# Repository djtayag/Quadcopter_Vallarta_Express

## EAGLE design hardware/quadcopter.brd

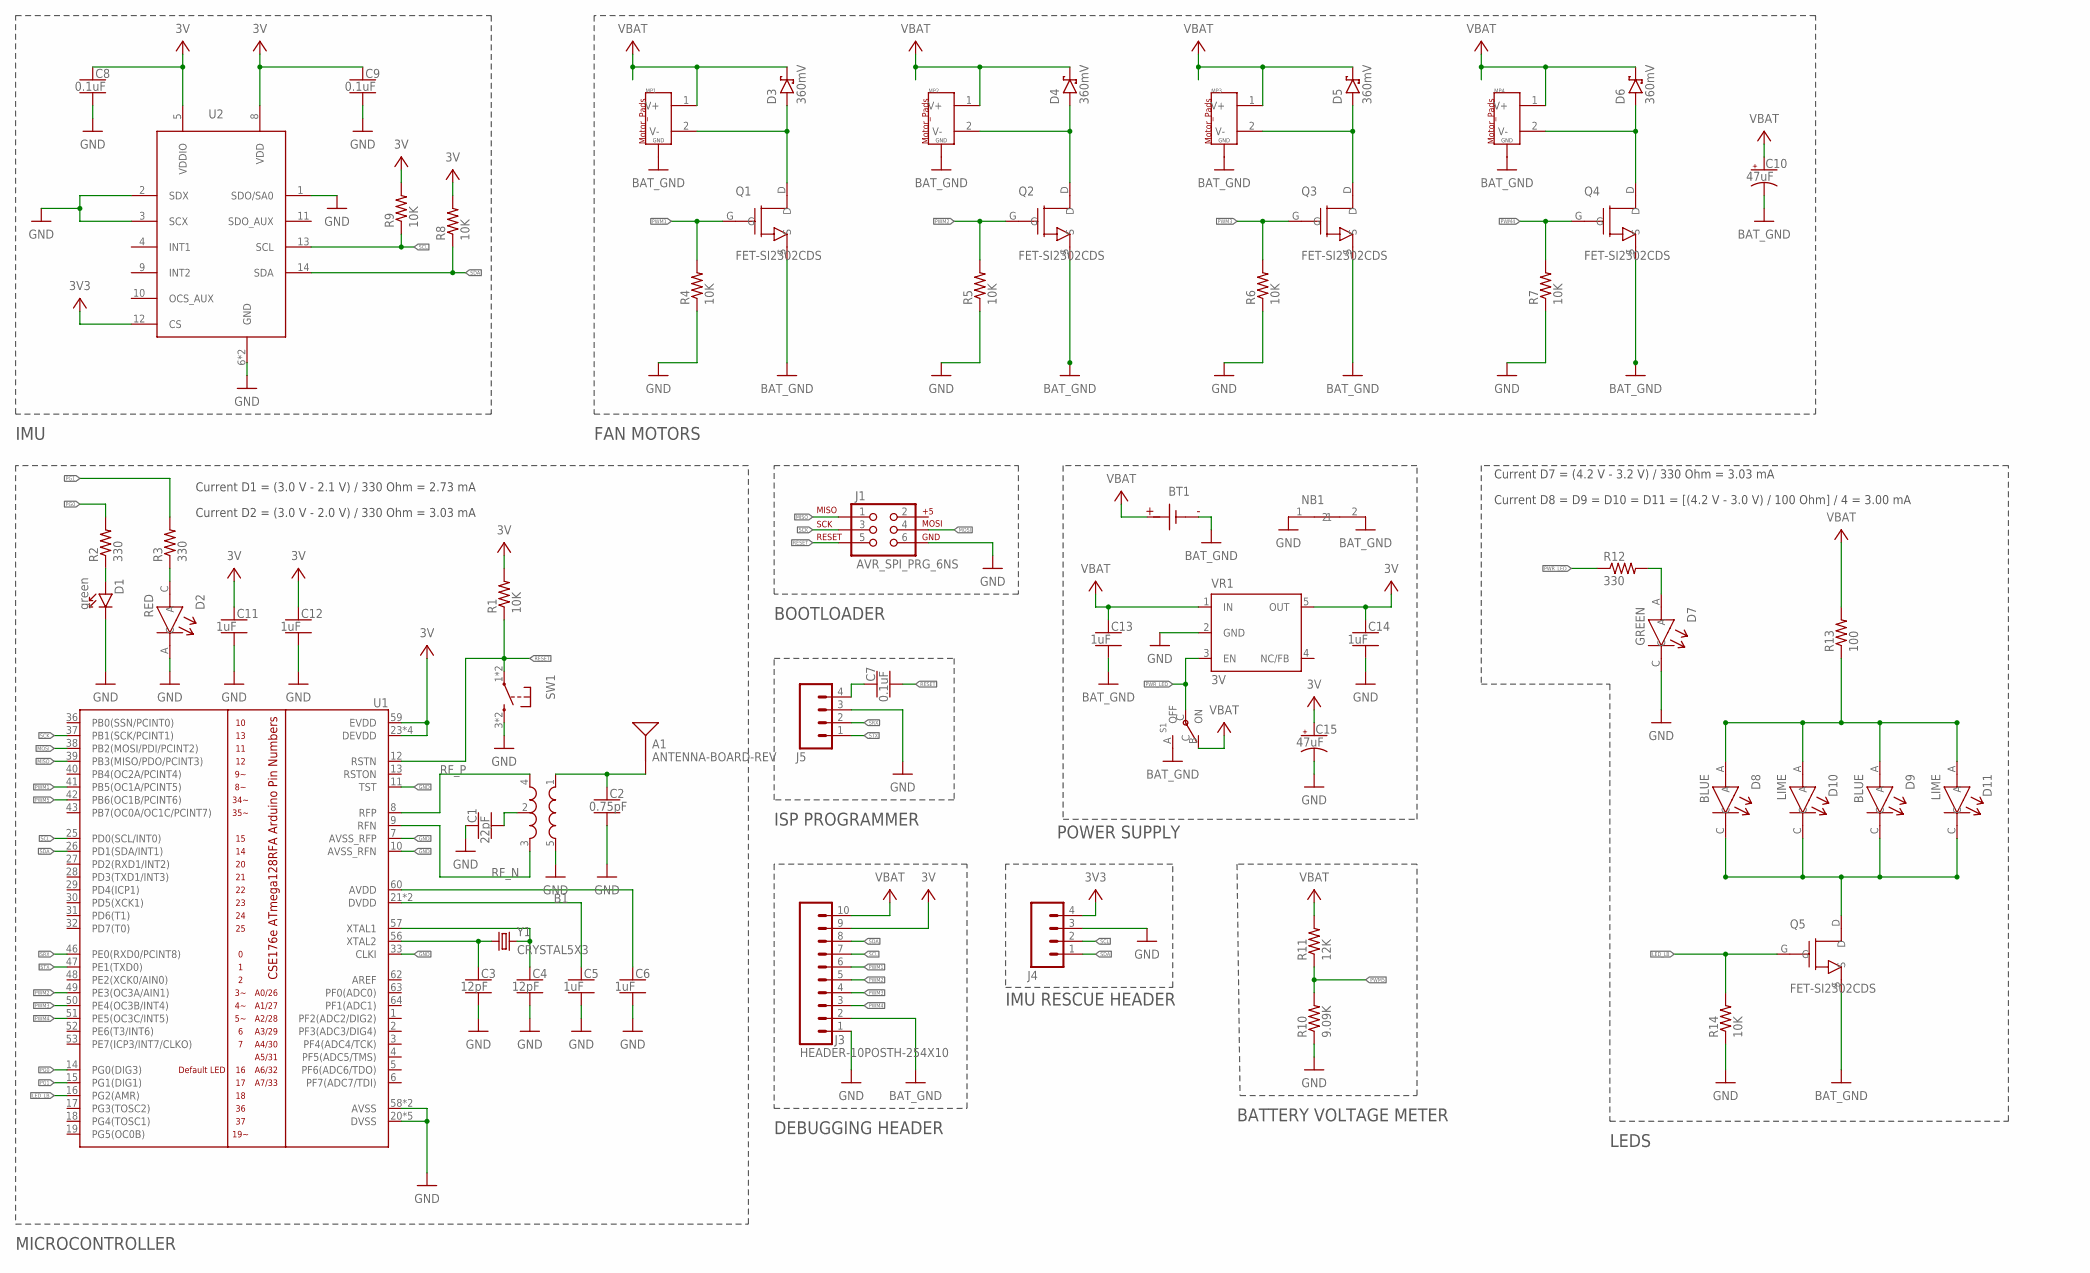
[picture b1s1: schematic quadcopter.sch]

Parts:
A1: ANTENNA-BOARD-REV; ANT_PCB_2.4GHZ_NRF8001_1.6MM_1OZ_REV
B1: BALUN0805; BALUN
BT1: BATTERY-SCREW-TERMINAL; SCREW-TERMINAL-1X2-2.54MM
C1: 22pF; CAPC2012X140_HS
C2: 0.75pF; CAPC2012X140_HS
C3, C4: 12pF; CAPC2012X140_HS
C5, C6, C11, C12, C13, C14: 1uF; CAPC2012X140_HS
C7, C8, C9: 0.1uF; CAPC2012X140_HS
C10, C15: 47uF; CAPMP3216X180
D1: green; LEDSC125X200X120-2_HS
D2: RED; 0805_LED
D3, D4, D5, D6: 360mV; SODFL3516X96
D7: GREEN; 0805_LED
D8, D9: BLUE; 1411_LED
D10, D11: LIME; 1411_LED
J1: AVR_SPI_PRG_6NS; 2X3-NS
J3: HEADER-10POSTH-254X10; HDRV10W63P254_10X1_2540X254H838_HS
J4: HEADER-4POS-0.1IN-FEMALE; HDRVR4W80P254_1X4_1066X254X850B
J5: HEADER-4POS-0.1IN-FEMALE-SMD-BOTTOM-ENTRY; HEADER-1X4-BOTTOM-ENTRY
MP1, MP2, MP3, MP4: MOTOR_PADS_GND-MOLEX-SMD; MOLEX-0532610271
NB1: NET-BRIDGE
Q1, Q2, Q3, Q4, Q5: FET-SI2302CDS; SI2302MOSFET
R1, R4, R5, R6, R7, R8, R9, R14: 10K; RESC2012X60_HS
R2, R3, R12: 330; RESC2012X60_HS
R10: 9.09K; RESC2012X60_HS
R11: 12K; RESC2012X60_HS
R13: 100; RESC2012X60_HS
S1: POWER-SWITCH-MFS201N-9-Z-SMD-EDGE; JS102011SAQN
SW1: PUSHBUTTON_SMD-VERTICAL-1; TE_FSM8JSMA_HS
U1: ATMEGA128RFA1; QFN-64
U2: IMU_LSM6DSOX-LSM6DSOXTR; LSM6DS0XTR
VR1: 3V; SOT23-DBV
Y1: CRYSTAL5X3; CRYSTAL-SMD-5X3

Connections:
3V3: C8.1, C9.1, C11.1, C12.1, C14.1, C15.1 (+), J3.9, J4.4, R1.2, R8.2, R9.2, U1.23 (DEVDD), U1.34 (DEVDD), U1.44 (DEVDD), U1.54 (DEVDD), U1.59 (EVDD), U2.5 (VDDIO), U2.8 (VDD), U2.12 (CS), VR1.5 (OUT)
BAT_GND: BT1.1 (N), C10.2 (-), C13.2, J3.2, MP1.G1 (GND), MP1.G2 (GND), MP2.G1 (GND), MP2.G2 (GND), MP3.G1 (GND), MP3.G2 (GND), MP4.G1 (GND), MP4.G2 (GND), NB1.2, Q1.S, Q2.S, Q3.S, Q4.S, Q5.S, S1.A (OFF)
GND: B1.5 (GND), C1.1, C2.2, C3.2, C4.2, C5.2, C6.2, C8.2, C9.2, C11.2, C12.2, C14.2, C15.2 (-), D1.C, D2.A (C), D7.C, J1.6, J3.1, J4.3, J5.3, NB1.1, R4.1, R5.1, R6.1, R7.1, R10.1, R14.1, SW1.3 (2), SW1.4 (2), U1.7 (AVSS_RFP), U1.10 (AVSS_RFN), U1.11 (TST), U1.20 (DVSS), U1.24 (DVSS), U1.33 (CLKI), U1.35 (DVSS), U1.45 (DVSS), U1.55 (DVSS), U1.58 (AVSS), U1.61 (AVSS), U2.1 (SDO/SA0), U2.2 (SDX), U2.3 (SCX), U2.6 (GND), U2.7 (GND), VR1.2 (GND)
LED_LB: Q5.G, R14.2, U1.16 (PG2(AMR))
MISO: J1.1, U1.39 (PB3(MISO/PDO/PCINT3))
MOSI: J1.4, U1.38 (PB2(MOSI/PDI/PCINT2))
unnamed: B1.2 (GND), C1.2
unnamed: A1.FEED, B1.1 (IN), C2.1
unnamed: D3.2 (A), MP1.2 (V-), Q1.D
unnamed: D1.A, R2.1
unnamed: C3.1, U1.56 (XTAL2), Y1.1
unnamed: C4.1, U1.57 (XTAL1), Y1.3 (2)
unnamed: C5.1, U1.21 (DVDD), U1.22 (DVDD)
unnamed: C6.1, U1.60 (AVDD)
unnamed: D4.2 (A), MP2.2 (V-), Q2.D
unnamed: D5.2 (A), MP3.2 (V-), Q3.D
unnamed: D6.2 (A), MP4.2 (V-), Q4.D
unnamed: C7.1, J5.4
unnamed: D2.C (A), R3.1
unnamed: D7.A, R12.2
unnamed: D8.A, D9.A, D10.A, D11.A, R13.1
unnamed: D8.C, D9.C, D10.C, D11.C, Q5.D
PG0: R2.2, U1.14 (PG0(DIG3))
PG1: R3.2, U1.15 (PG1(DIG1))
PWM1: J3.6, Q1.G, R4.2, U1.41 (PB5(OC1A/PCINT5))
PWM2: J3.5, Q2.G, R5.2, U1.49 (PE3(OC3A/AIN1))
PWM3: J3.4, Q3.G, R6.2, U1.50 (PE4(OC3B/INT4))
PWM4: J3.3, Q4.G, R7.2, U1.51 (PE5(OC3C/INT5))
PWM5: R10.2, R11.1, U1.42 (PB6(OC1B/PCINT6))
PWR_LED: R12.1, S1.C, VR1.3 (EN)
RESET: C7.2, J1.5, R1.1, SW1.1, SW1.2 (1), U1.12 (RSTN)
RF_N: B1.3 (OUT2), U1.9 (RFN)
RF_P: B1.4 (OUT1), U1.8 (RFP)
SCK: J1.3, U1.37 (PB1(SCK/PCINT1))
SCL: J3.7, J4.2, R9.1, U1.25 (PD0(SCL/INT0)), U2.13 (SCL)
SDA: J3.8, J4.1, R8.1, U1.26 (PD1(SDA/INT1)), U2.14 (SDA)
SRX: J5.2, U1.46 (PE0(RXD0/PCINT8))
STX: J5.1, U1.47 (PE1(TXD0))
VBAT: BT1.2, C10.1 (+), C13.1, D3.1 (C), D4.1 (C), D5.1 (C), D6.1 (C), J3.10, MP1.1 (V+), MP2.1 (V+), MP3.1 (V+), MP4.1 (V+), R11.2, R13.2, S1.B (ON), VR1.1 (IN)

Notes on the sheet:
MICROCONTROLLER
BOOTLOADER
ISP PROGRAMMER
IMU
FAN MOTORS
DEBUGGING HEADER
IMU RESCUE HEADER
POWER SUPPLY
BATTERY VOLTAGE METER
LEDS
Current D1 = (3.0 V - 2.1 V) / 330 Ohm = 2.73 mA
Current D2 = (3.0 V - 2.0 V) / 330 Ohm = 3.03 mA
Current D7 = (4.2 V - 3.2 V) / 330 Ohm = 3.03 mA
Current D8 = D9 = D10 = D11 = [(4.2 V - 3.0 V) / 100 Ohm] / 4 = 3.00 mA

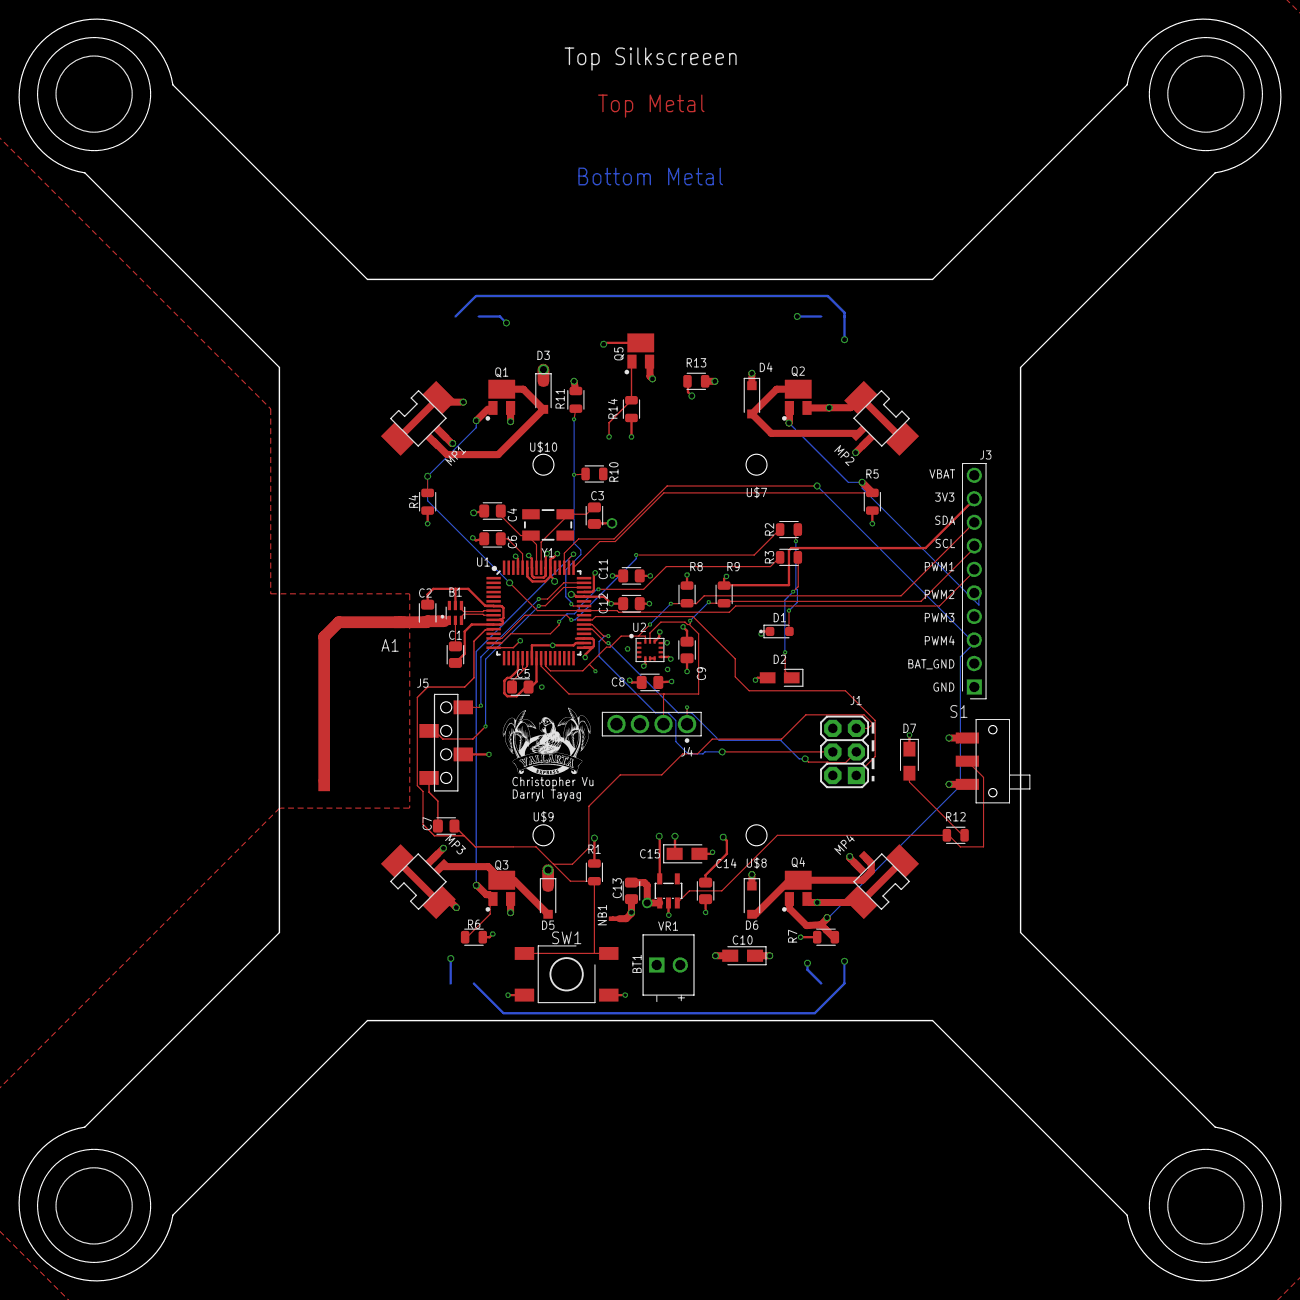
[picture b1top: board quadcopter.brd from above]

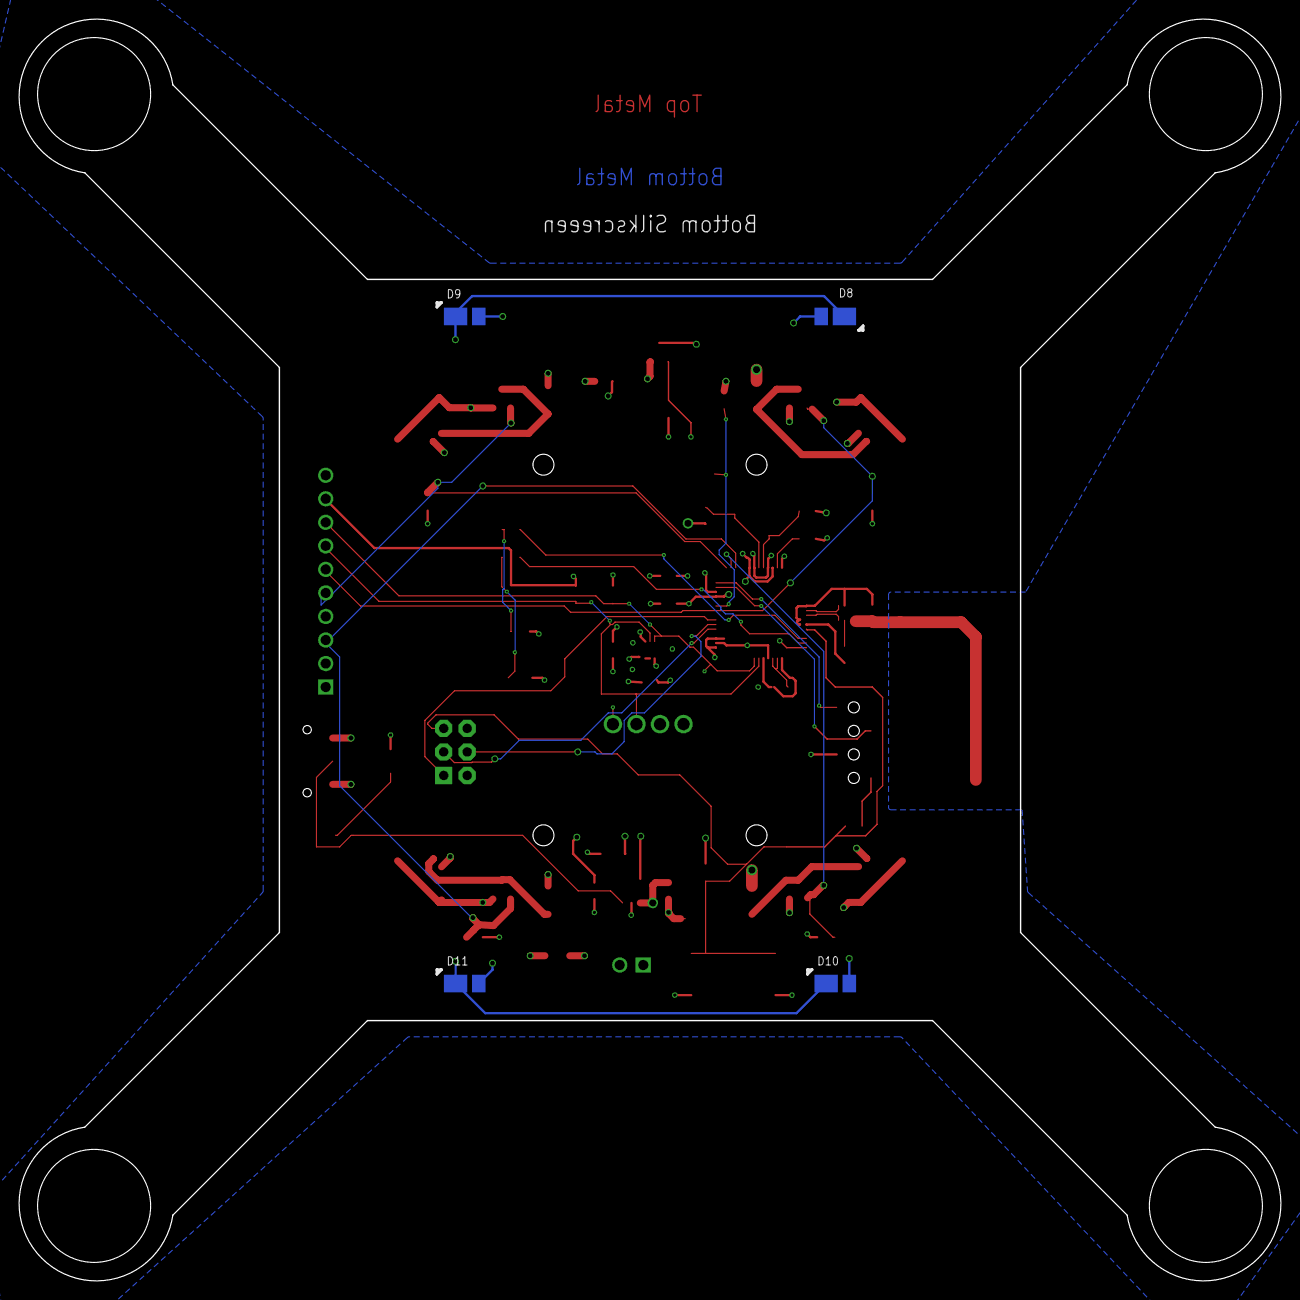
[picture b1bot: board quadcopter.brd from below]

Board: 4 copper layers, 136.2 x 136.2 mm, 73 parts (4 on the bottom side), 39 nets.

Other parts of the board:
U$1: LAYER_LABELS
U$2, U$3, U$4, U$5: MOTOR_AND_PROP
U$6: VALLARTAEXPRESS_LOGO
U$7, U$8, U$9, U$10: 2-56-MOUNTING-HOLE-NO-METAL
